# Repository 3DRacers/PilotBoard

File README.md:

# 3DRacers PilotBoard
The first 3D Printed Racing Game, Smartphone-driven and Arduino-compatible

## The Game

- Race with your friends (up to 1000 players)
- Drive with the Android/Iphone app or the 3D printed remote
- Watch real time score boards and lap times: each car has a sensor that detect specially designed gates.
- Re-program the Arduino core inside each car to unlock new features from the community

More info on: [3DRacers website]

Follow us on Twitter: [@3dracers] and on our community [forum].

Author: Marco D'Alia [@madarco]

## The Arduino code

If you purchased a 3Racers Pilot, you'll find it already programmed with the standard RacerOS code (Arduino-compatible).

However, if you created your own 3DRacers Pilot variation, or you want to modify the Arduino code, go to the

[Lib3DRacers repository] and download the code from there.

# The proto shield

3DRacers Pilot boards support shields, like a standard Arduino. The proto shield is the simpliest shield, that allows soldering of trought-hole components or connectors, but you can use the Eagle file as a template to create your own shield.

### Development

Want to contribute? Great!

Just fork this repo or create an issue.
Also, follow the community [forum]

License
----

Creative Commons Share-Alike 4.0

**Open Hardware, Hell Yeah!**

[//]: # (These are reference links used in the body of this note and get stripped out when the markdown processor does it's job. There is no need to format nicely because it shouldn't be seen. Thanks SO - http://stackoverflow.com/questions/4823468/store-comments-in-markdown-syntax)

   [forum]: <http://forum.3dracers.com>
   [Lib3DRacers repository]: <https://github.com/3DRacers/Lib3DRacers>
   [3DRacers website]: <http://www.3dracers.com>
   [@madarco]: <http://twitter.com/madarco>
   [@3dracers]: <http://twitter.com/3dracers>

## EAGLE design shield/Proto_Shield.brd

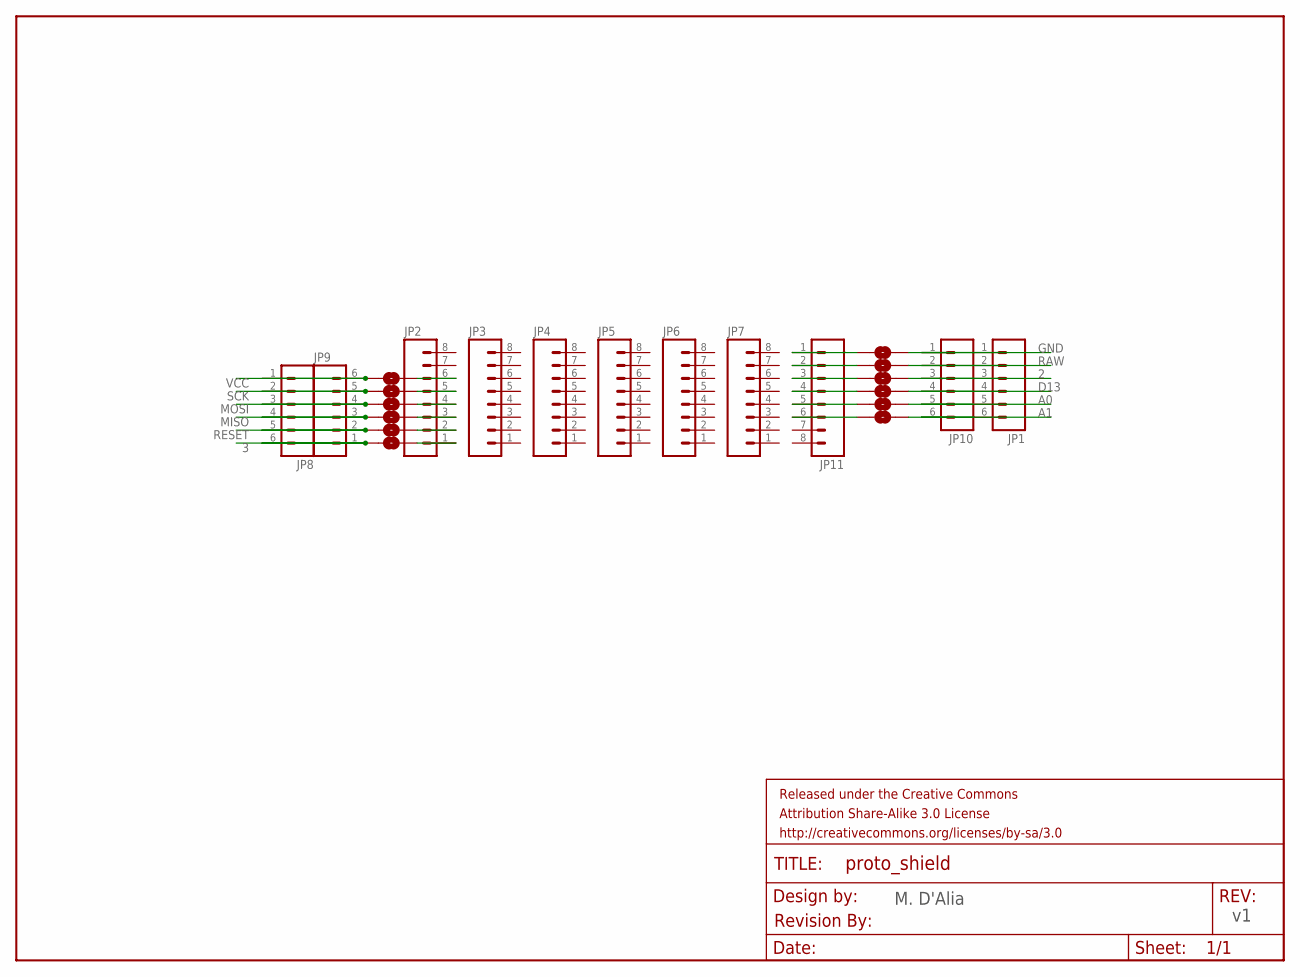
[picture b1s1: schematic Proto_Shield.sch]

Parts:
FRAME1: FRAME-LETTER; CREATIVE_COMMONS
JP1: M06SMD-STRAIGHT; 1X06_SMD_STRAIGHT
JP2, JP3, JP4, JP5, JP6, JP7, JP11: M08NO_SILK; 1X08_NO_SILK
JP8: M06SMD-STRAIGHT-ALT-NOSILK; 1X06_SMD_STRAIGHT_ALT_NOSILK
JP9, JP10: M06LOCK_LONGPADS; 1X06_LOCK_LONGPADS
SJ1, SJ2, SJ3, SJ4, SJ5, SJ6, SJ7, SJ8, SJ9, SJ10, SJ11, SJ12: SOLDERJUMPERTRACE; SJ_2S-TRACE
U$5: REVISION

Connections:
2: JP1.3, JP10.3, SJ4.1
3: JP8.6, JP9.1, SJ12.2
A0: JP1.5, JP10.5, SJ2.1
A1: JP1.6, JP10.6, SJ1.1
D13: JP1.4, JP10.4, SJ3.1
GND: JP1.1, JP10.1, SJ6.1
MISO: JP8.4, JP9.3, SJ10.2
MOSI: JP8.3, JP9.4, SJ9.2
unnamed: JP11.6, SJ1.2
unnamed: JP11.5, SJ2.2
unnamed: JP11.4, SJ3.2
unnamed: JP11.3, SJ4.2
unnamed: JP11.2, SJ5.2
unnamed: JP11.1, SJ6.2
unnamed: JP2.6, SJ7.1
unnamed: JP2.5, SJ8.1
unnamed: JP2.4, SJ9.1
unnamed: JP2.3, SJ10.1
unnamed: JP2.2, SJ11.1
unnamed: JP2.1, SJ12.1
RAW: JP1.2, JP10.2, SJ5.1
RESET: JP8.5, JP9.2, SJ11.2
SCK: JP8.2, JP9.5, SJ8.2
VCC: JP8.1, JP9.6, SJ7.2

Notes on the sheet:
M. D'Alia

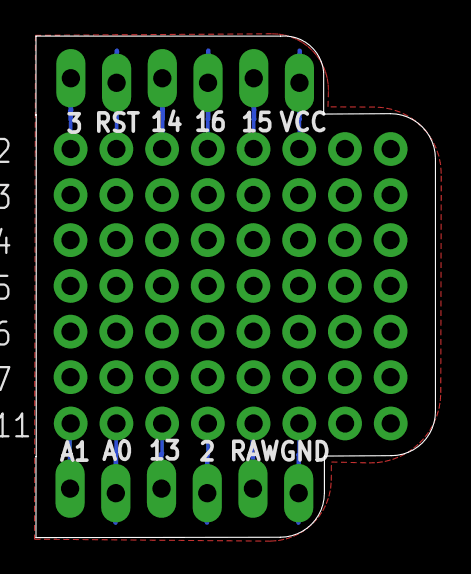
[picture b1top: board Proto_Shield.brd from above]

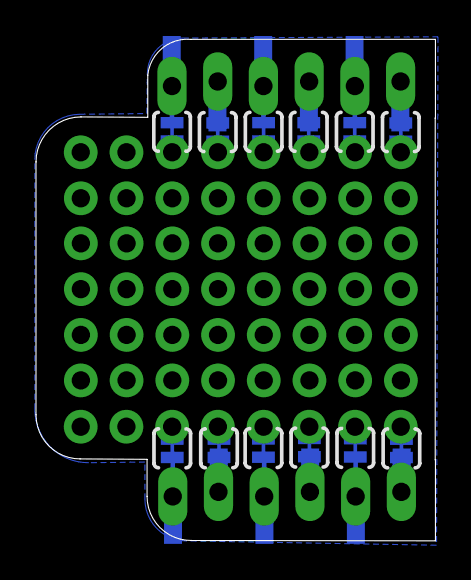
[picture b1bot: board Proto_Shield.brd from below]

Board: 2 copper layers, 22.2 x 27.9 mm, 25 parts (14 on the bottom side), 24 nets.

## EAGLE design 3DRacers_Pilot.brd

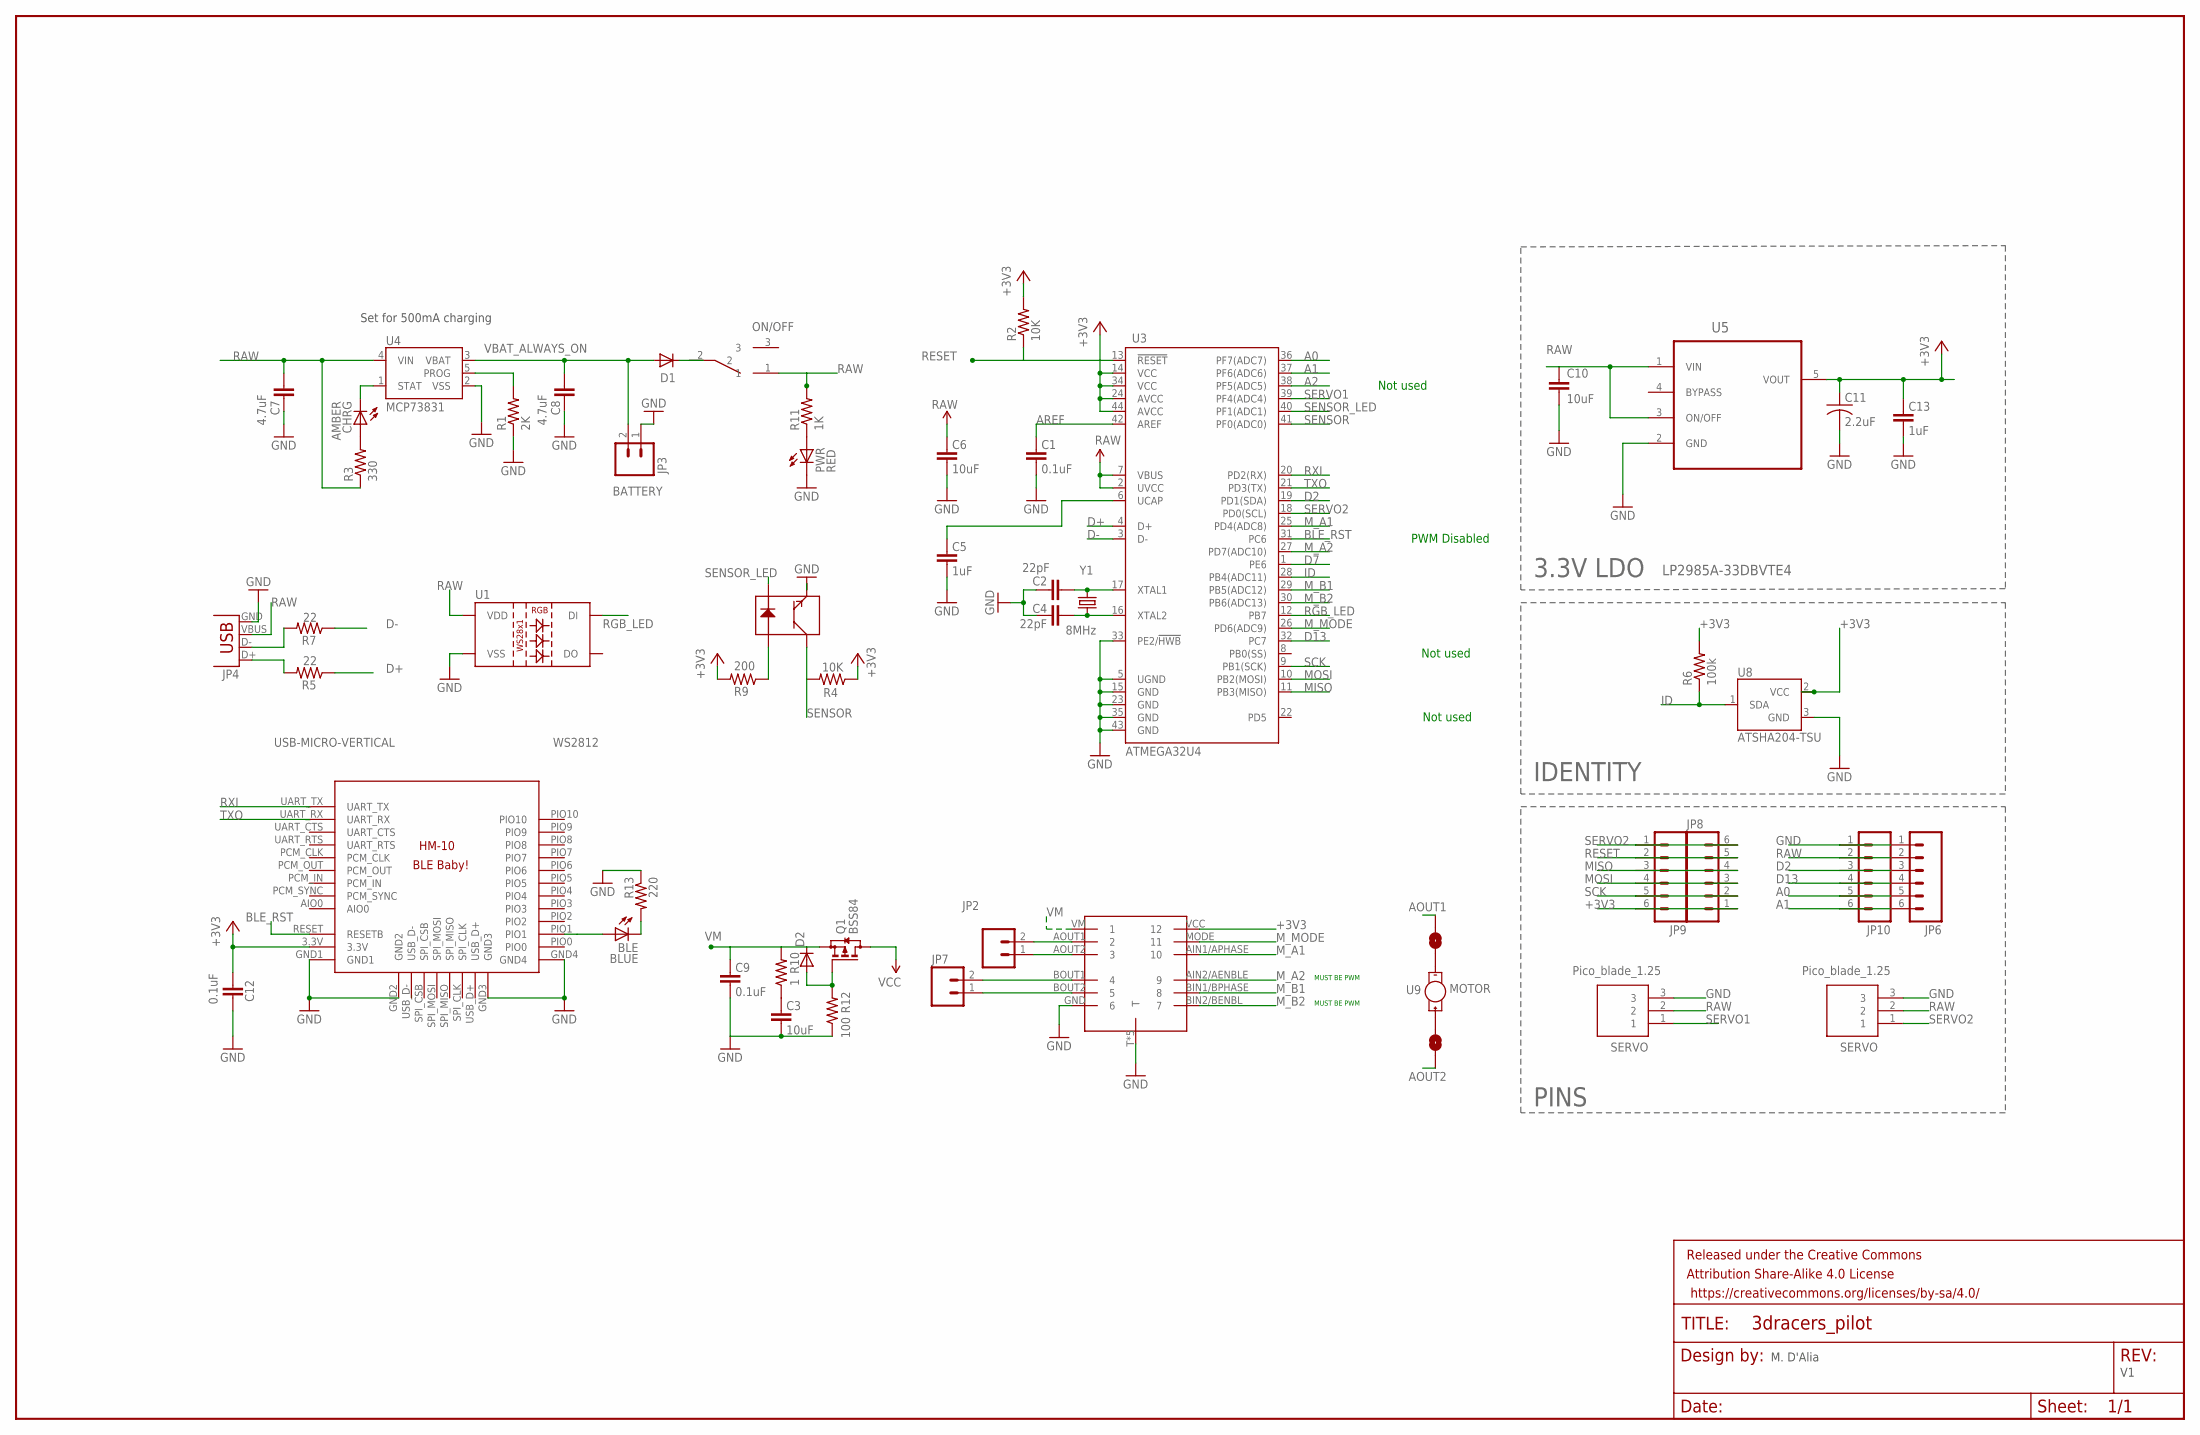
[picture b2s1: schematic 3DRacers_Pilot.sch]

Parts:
BLE: BLUE; LED-0603
C1, C9, C12: 0.1uF; 0603-CAP
C2, C4: 22pF; 0603-CAP
C3: 10uF; 0805
C5: 1uF; 0603-CAP
C6: 10uF; 0603-CAP
C7, C8: 4.7uF; 0603-CAP
C10: 10uF; 0805; MPN 06036D105KAT2A
C11: 2.2uF; C0603K; MPN 0603YD225MAT2A
C13: 1uF; 0805
CHRG: AMBER; LED-0603
D1, D2: DIODESOD; SOD-323
FRAME2: FRAME-LEDGER; CREATIVE_COMMONS
JP2, JP7: M021X02_NO_SILK; 1X02_NO_SILK
JP3: M02JST-PTH-VERT; JST-2-PTH-VERT
JP4: USB-MICRO-VERTICAL
JP6: M06SMD-STRAIGHT; 1X06_SMD_STRAIGHT
JP8: M06SMD-STRAIGHT-ALT-NOSILK; 1X06_SMD_STRAIGHT_ALT_NOSILK
JP9, JP10: M06LOCK_LONGPADS; 1X06_LOCK_LONGPADS
K2, K3: PICO_BLADE_1.25
PWR: RED; LED-0603
Q1: BSS84; SOT23
R1: 2K; 0603-RES
R2, R4: 10K; 0603-RES
R3: 330; 0603-RES
R5, R7: 22; 0603-RES
R6: 100k; 0603-RES
R9: 200; 0603-RES
R10: 1; 0603-RES
R11: 1K; 0603-RES
R12: 100; 0603-RES
R13: 220; 0603-RES; MPN 0.87.0022.0
SJ1, SJ2: SOLDERJUMPERTRACE; SJ_2S-TRACE
U1: WS2812; LED-TRICOLOR-5050-IC
U3: ATMEGA32U4; QFN-44-NOPAD_1:1-OUTFAKES
U4: MCP73831; SOT23-5
U5: LP2985A-33DBVTE4; SOT95P280X145-5N
U6: QRE1113
U7: DRC8835; DRV8835
U8: ATSHA204-TSU; SOT23-3
U9: MOTOR; MOTOR-6MM-THT
U$2: BLE-HM-10-3DRMODIFIED-FOR-3DRACERS; BLE-HM-10-3DR
U$3: SWITCH; 3DRACERS_SWITCH
Y1: 8MHz; CRYSTAL-SMD-5X3

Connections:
+3V3: C11.1, C12.1, C13.2, JP8.1, JP9.6, R2.2, R4.1, R6.2, R9.2, U3.14 (VCC), U3.24 (AVCC), U3.34 (VCC), U3.44 (AVCC), U5.5 (VOUT), U7.VCC (12), U8.2 (VCC), U$2.3.3V
A0: JP6.5, JP10.5, U3.36 (PF7(ADC7))
A1: JP6.6, JP10.6, U3.37 (PF6(ADC6))
A2: U3.38 (PF5(ADC5))
AOUT1: JP7.2, SJ1.2, U7.BOUT1 (4)
AOUT2: JP7.1, SJ2.2, U7.BOUT2 (5)
AREF: C1.2, U3.42 (AREF)
BLE_CON: BLE.A, U$2.PIO1
BLE_RST: U3.31 (PC6), U$2.RESET (RESETB)
BOUT1: JP2.2, U7.AOUT1 (2)
D2: JP6.3, JP10.3, U3.19 (PD1(SDA))
D7: U3.1 (PE6)
D13: JP6.4, JP10.4, U3.32 (PC7)
D+: R5.1, U3.4 (D+)
D-: R7.1, U3.3 (D-)
GND: C1.1, C2.2, C3.1, C4.2, C5.1, C6.1, C7.2, C8.2, C9.1, C10.2, C11.2, C12.2, C13.1, JP3.1, JP4.GND, JP6.1, JP10.1, K2.3, K3.3, PWR.C, R1.1, R12.1, R13.1, U1.6 (VSS), U3.5 (UGND), U3.15 (GND), U3.23 (GND), U3.33 (PE2/!HWB), U3.35 (GND), U3.43 (GND), U4.2 (VSS), U5.2 (GND), U6.4 (E), U7.GND (6), U7.T, U7.T@12 (T), U7.T@15 (T), U7.T@16 (T), U7.T@17 (T), U8.3 (GND), U$2.GND1, U$2.GND2, U$2.GND3, U$2.GND4
ID: R6.1, U3.28 (PB4(ADC11)), U8.1 (SDA)
MISO: JP8.4, JP9.3, U3.11 (PB3(MISO))
MOSI: JP8.3, JP9.4, U3.10 (PB2(MOSI))
M_A1: U3.25 (PD4(ADC8)), U7.AIN1/APHASE (10)
M_A2: U3.27 (PD7(ADC10)), U7.AIN2/AENBLE (9)
M_B1: U3.29 (PB5(ADC12)), U7.BIN1/BPHASE (8)
M_B2: U3.30 (PB6(ADC13)), U7.BIN2/BENBL (7)
M_MODE: U3.26 (PD6(ADC9)), U7.MODE (11)
unnamed: C4.1, U3.16 (XTAL2), Y1.1
unnamed: C2.1, U3.17 (XTAL1), Y1.3 (2)
unnamed: JP4.D-, R7.2
unnamed: C5.2, U3.6 (UCAP)
unnamed: R9.1, U6.1 (A)
unnamed: SJ1.1, U9.-
unnamed: JP4.D+, R5.2
unnamed: CHRG.A, R3.2
unnamed: JP2.1, U7.AOUT2 (3)
unnamed: D2.2 (A), Q1.1 (G), R12.2
unnamed: C3.2, R10.1
unnamed: SJ2.1, U9.+
unnamed: D1.1 (C), U$3.2
unnamed: BLE.C, R13.2
unnamed: PWR.A, R11.1
PROG: R1.2, U4.5 (PROG)
RAW: C6.2, C7.1, C10.1, JP4.VBUS, JP6.2, JP10.2, K2.2, K3.2, Q1.3 (D), R3.1, R11.2, U1.3 (VDD), U1.5 (VDD), U3.2 (UVCC), U3.7 (VBUS), U4.4 (VIN), U5.1 (VIN), U5.3 (ON/OFF), U$3.1
RESET: JP8.5, JP9.2, R2.1, U3.13 (!RESET)
RGB_LED: U1.2 (DI), U3.12 (PB7)
RXI: U3.20 (PD2(RX)), U$2.UART_TX
SCK: JP8.2, JP9.5, U3.9 (PB1(SCK))
SENSOR: R4.2, U3.41 (PF0(ADC0)), U6.3 (C)
SENSOR_LED: U3.40 (PF1(ADC1)), U6.2 (K)
SERVO1: K2.1, U3.39 (PF4(ADC4))
SERVO2: JP8.6, JP9.1, K3.1, U3.18 (PD0(SCL))
STAT: CHRG.C, U4.1 (STAT)
TXO: U3.21 (PD3(TX)), U$2.UART_RX
VBAT_ALWAYS_ON: C8.1, D1.2 (A), JP3.2, U4.3 (VBAT)
VM: C9.2, D2.1 (C), Q1.2 (S), R10.2, U7.VM (1)

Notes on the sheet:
Set for 500mA charging
MUST BE PWM
ON/OFF
BATTERY
3.3V LDO
PINS
IDENTITY
Not used
PWM Disabled
M. D'Alia

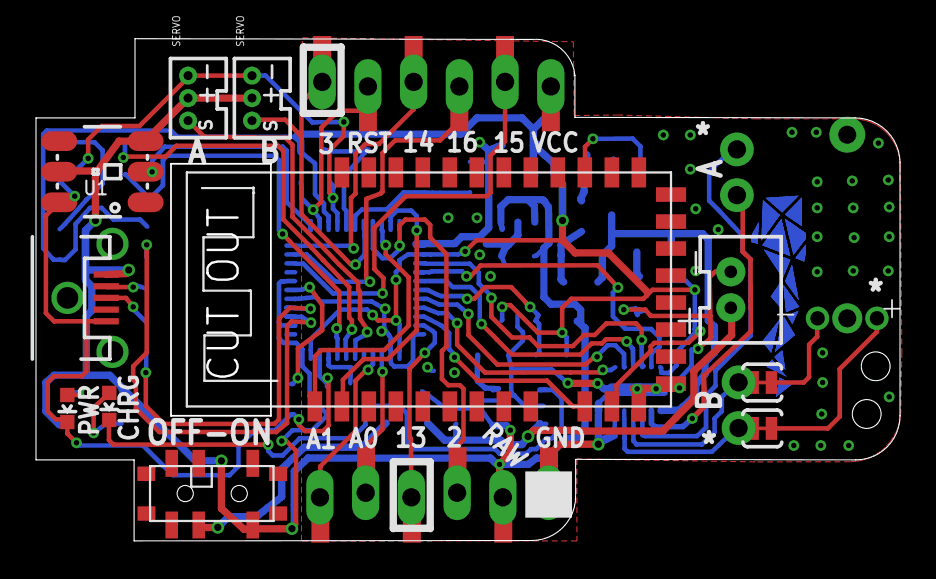
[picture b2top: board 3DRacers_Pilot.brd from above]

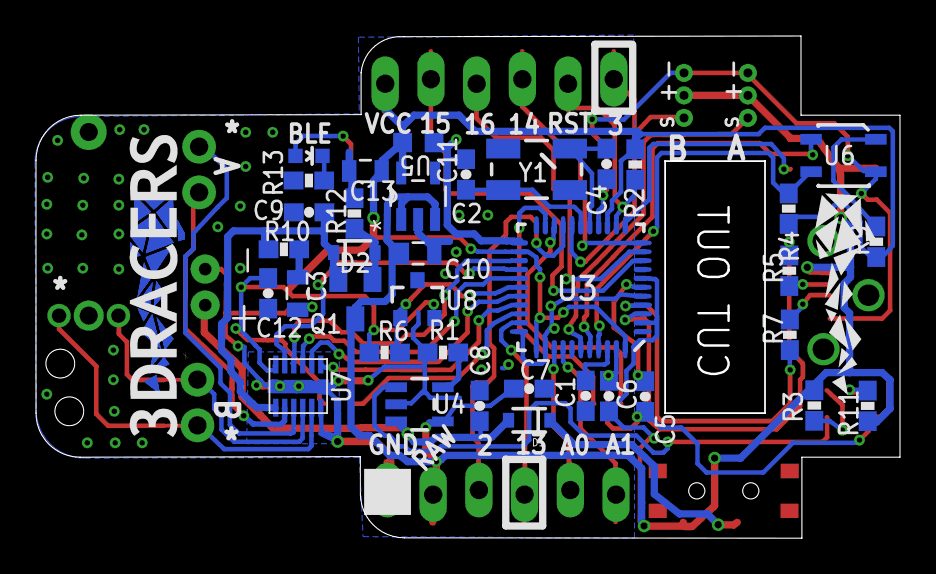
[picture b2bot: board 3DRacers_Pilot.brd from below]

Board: 2 copper layers, 47.9 x 27.8 mm, 55 parts (37 on the bottom side), 51 nets.

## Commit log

2015-10-13 Initial commit with Pilot and Proto Shield
2015-10-13 Fixed proto shield image
2015-10-13 Smaller pictures
2015-10-13 Bottom view first
2015-10-20 Created LICENSE file

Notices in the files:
parts and their libraries:
SparkFun-Sensors: Licensing: Creative Commons ShareAlike 4.0 International - https://creativecommons.org/licenses/by-sa/4.0
SparkFun-LED: Licensing: CC v3.0 Share-Alike You are welcome to use this library for commercial purposes.
SparkFun-Aesthetics: https://creativecommons.org/licenses/by-sa/4.0
